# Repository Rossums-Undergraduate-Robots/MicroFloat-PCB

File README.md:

# MicroFloat-PCB
PCB CAD for MicroFloat

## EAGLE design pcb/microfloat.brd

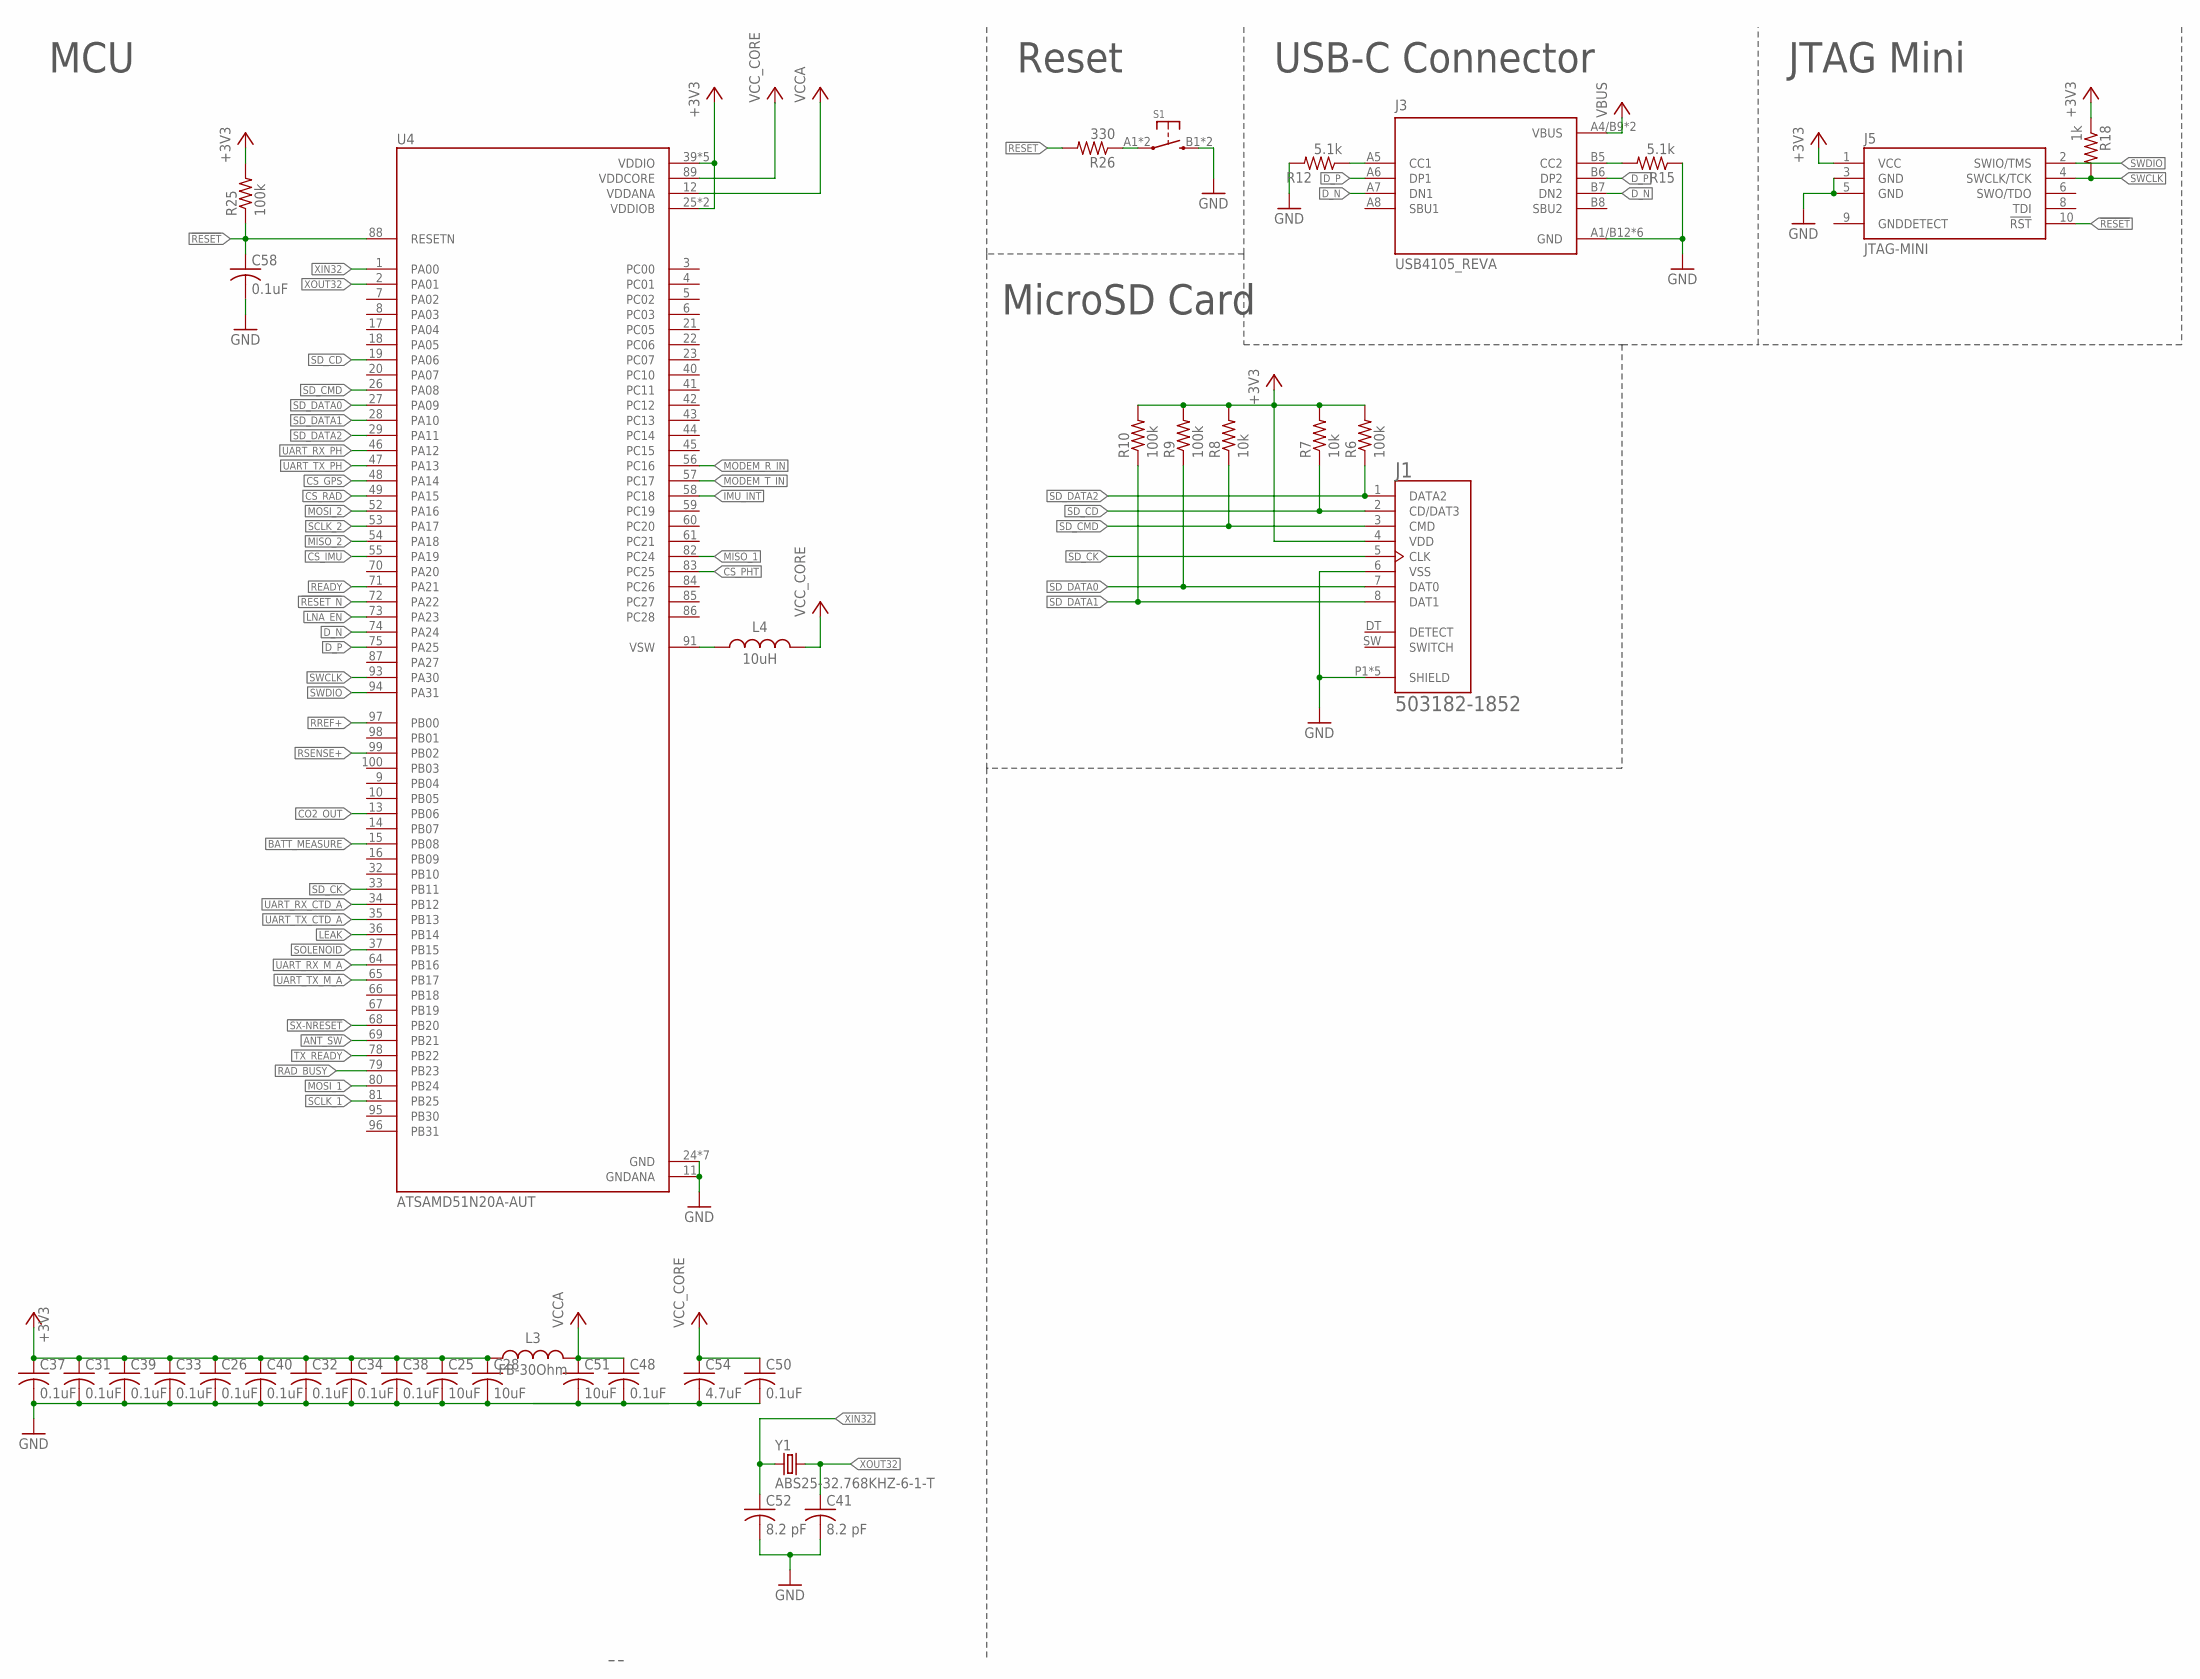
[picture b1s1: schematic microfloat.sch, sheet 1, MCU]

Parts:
C25, C28, C51: 10uF; C0805; TOLERANCE 5%; VOLTAGE 10V
C26, C31, C32, C33, C34, C37, C38, C39, C40, C48, C50, C58: 0.1uF; C0603; TOLERANCE 5%; VOLTAGE 10V
C41, C52: 8.2 pF; C0603; TOLERANCE 0.5%; VOLTAGE 10V
C54: 4.7uF; C0603; TOLERANCE 5%; VOLTAGE 10V
J1: 503182-1852; MOLEX_503182-1852
J3: USB4105_REVA; GCT_USB4105_REVA
J5: JTAG-MINI; FTSH-105-01-F-D-K
L3: FB-30Ohm; 0805; TOLERANCE 25%
L4: 10uH; 78438336100; TOLERANCE 10%
R6, R9, R10, R25: 100k; R0603; TOLERANCE 1%
R7, R8: 10k; R0603; TOLERANCE 1%
R12, R15: 5.1k; R0603; TOLERANCE 0.1%
R18: 1k; R0603; TOLERANCE 1%
R26: 330; R0603; TOLERANCE 1%
S1: BTN_10-XXSMD; TACTILE_SWITCH_SMD_6.2MM_TALL
U4: ATSAMD51N20A-AUT; QFP50P1600X1600X120-100N
Y1: ABS25-32.768KHZ-6-1-T; XTAL_ABS25-32.768KHZ-6-1-T

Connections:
!RESET: C58.1, J5.10 (!RST), R25.1, R26.2, U4.88 (RESETN)
!RESET_N: U4.72 (PA22); also elsewhere on the board
!SX-NRESET: U4.68 (PB20); also elsewhere on the board
+3V3: C25.1, C26.1, C28.1, C31.1, C32.1, C33.1, C34.1, C37.1, C38.1, C39.1, C40.1, J1.4 (VDD), J5.1 (VCC), L3.1, R6.2, R7.2, R8.2, R9.2, R10.2, R18.1, R25.2, U4.25 (VDDIOB), U4.30 (VDDIOB), U4.39 (VDDIO), U4.51 (VDDIO), U4.63 (VDDIO), U4.77 (VDDIO), U4.92 (VDDIO); also elsewhere on the board
ANT_SW: U4.69 (PB21); also elsewhere on the board
BATT_MEASURE: U4.15 (PB08); also elsewhere on the board
CO2_OUT: U4.13 (PB06); also elsewhere on the board
CS_GPS: U4.48 (PA14); also elsewhere on the board
CS_IMU: U4.55 (PA19); also elsewhere on the board
CS_PHT: U4.83 (PC25); also elsewhere on the board
CS_RAD: U4.49 (PA15); also elsewhere on the board
D_N: J3.A7 (DN1), J3.B7 (DN2), U4.74 (PA24)
D_P: J3.A6 (DP1), J3.B6 (DP2), U4.75 (PA25)
GND: C25.2, C26.2, C28.2, C31.2, C32.2, C33.2, C34.2, C37.2, C38.2, C39.2, C40.2, C41.2, C48.2, C50.2, C51.2, C52.2, C54.2, C58.2, J1.6 (VSS), J1.P1 (SHIELD), J1.P2 (SHIELD), J1.P3 (SHIELD), J1.P4 (SHIELD), J1.P5 (SHIELD), J3.A1/B12 (GND), J3.B1/A12 (GND), J3.G1 (GND), J3.G2 (GND), J3.G3 (GND), J3.G4 (GND), J5.3 (GND), J5.5 (GND), R12.2, R15.1, S1.B1 (S), S1.B2 (S), U4.11 (GNDANA), U4.24 (GND), U4.31 (GND), U4.38 (GND), U4.50 (GND), U4.62 (GND), U4.76 (GND), U4.90 (GND); also elsewhere on the board
IMU_INT: U4.58 (PC18); also elsewhere on the board
LEAK: U4.36 (PB14); also elsewhere on the board
LNA_EN: U4.73 (PA23); also elsewhere on the board
MISO_1: U4.82 (PC24); also elsewhere on the board
MISO_2: U4.54 (PA18); also elsewhere on the board
MODEM_R_IN: U4.56 (PC16); also elsewhere on the board
MODEM_T_IN: U4.57 (PC17); also elsewhere on the board
MOSI_1: U4.80 (PB24); also elsewhere on the board
MOSI_2: U4.52 (PA16); also elsewhere on the board
unnamed: J3.B5 (CC2), R15.2
unnamed: J3.A5 (CC1), R12.1
unnamed: L4.2, U4.91 (VSW)
unnamed: R26.1, S1.A1, S1.A2
RAD_BUSY: U4.79 (PB23); also elsewhere on the board
READY: U4.71 (PA21); also elsewhere on the board
RREF+: U4.97 (PB00); also elsewhere on the board
RSENSE+: U4.99 (PB02); also elsewhere on the board
SCLK_1: U4.81 (PB25); also elsewhere on the board
SCLK_2: U4.53 (PA17); also elsewhere on the board
SD_CD: J1.2 (CD/DAT3), R7.1, U4.19 (PA06)
SD_CK: J1.5 (CLK), U4.33 (PB11)
SD_CMD: J1.3 (CMD), R8.1, U4.26 (PA08)
SD_DATA0: J1.7 (DAT0), R9.1, U4.27 (PA09)
SD_DATA1: J1.8 (DAT1), R10.1, U4.28 (PA10)
SD_DATA2: J1.1 (DATA2), R6.1, U4.29 (PA11)
SOLENOID: U4.37 (PB15); also elsewhere on the board
SWCLK: J5.4 (SWCLK/TCK), R18.2, U4.93 (PA30)
SWDIO: J5.2 (SWIO/TMS), U4.94 (PA31)
TX_READY: U4.78 (PB22); also elsewhere on the board
UART_RX_CTD_A: U4.34 (PB12); also elsewhere on the board
UART_RX_M_A: U4.64 (PB16); also elsewhere on the board
UART_RX_PH: U4.46 (PA12); also elsewhere on the board
UART_TX_CTD_A: U4.35 (PB13); also elsewhere on the board
UART_TX_M_A: U4.65 (PB17); also elsewhere on the board
UART_TX_PH: U4.47 (PA13); also elsewhere on the board
VBUS: J3.A4/B9 (VBUS), J3.B4/A9 (VBUS); also elsewhere on the board
VCCA: C48.1, C51.1, L3.2, U4.12 (VDDANA)
VCC_CORE: C50.1, C54.1, L4.1, U4.89 (VDDCORE)
XIN32: C52.1, U4.1 (PA00), Y1.1
XOUT32: C41.1, U4.2 (PA01), Y1.4 (2)

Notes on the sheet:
MCU
Reset
MicroSD Card
USB-C Connector
JTAG Mini

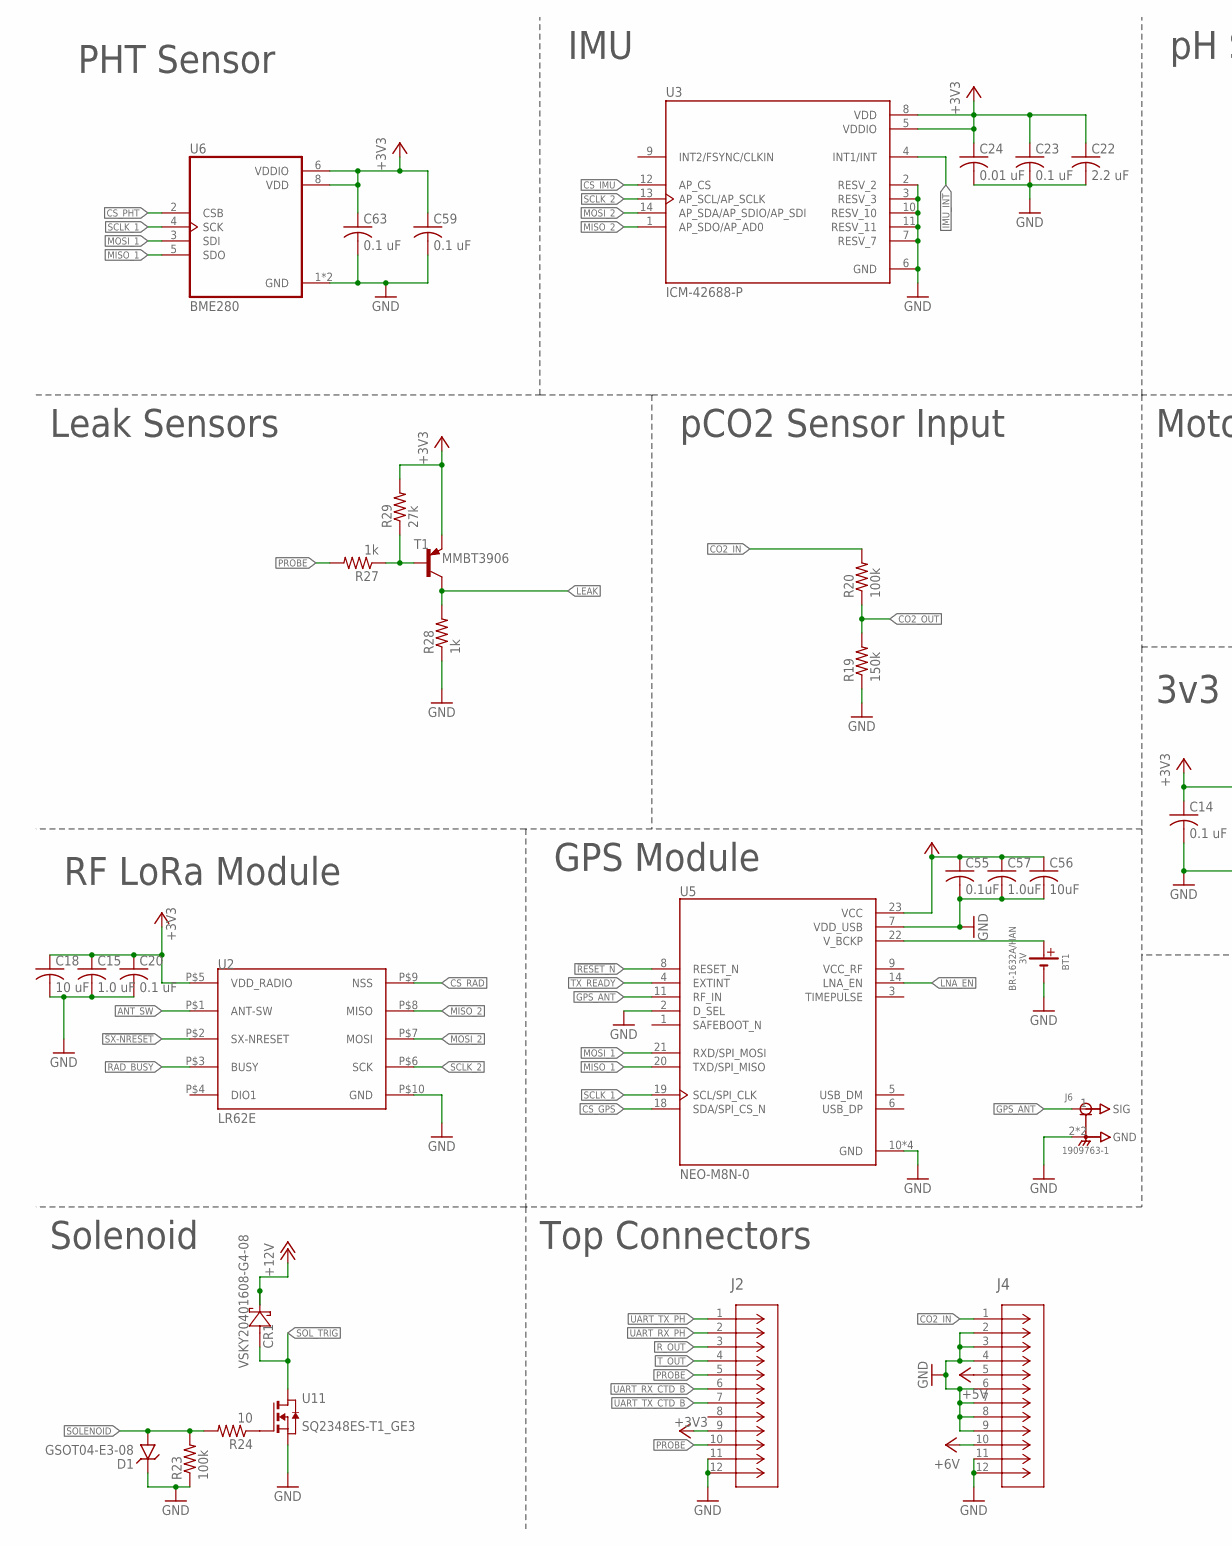
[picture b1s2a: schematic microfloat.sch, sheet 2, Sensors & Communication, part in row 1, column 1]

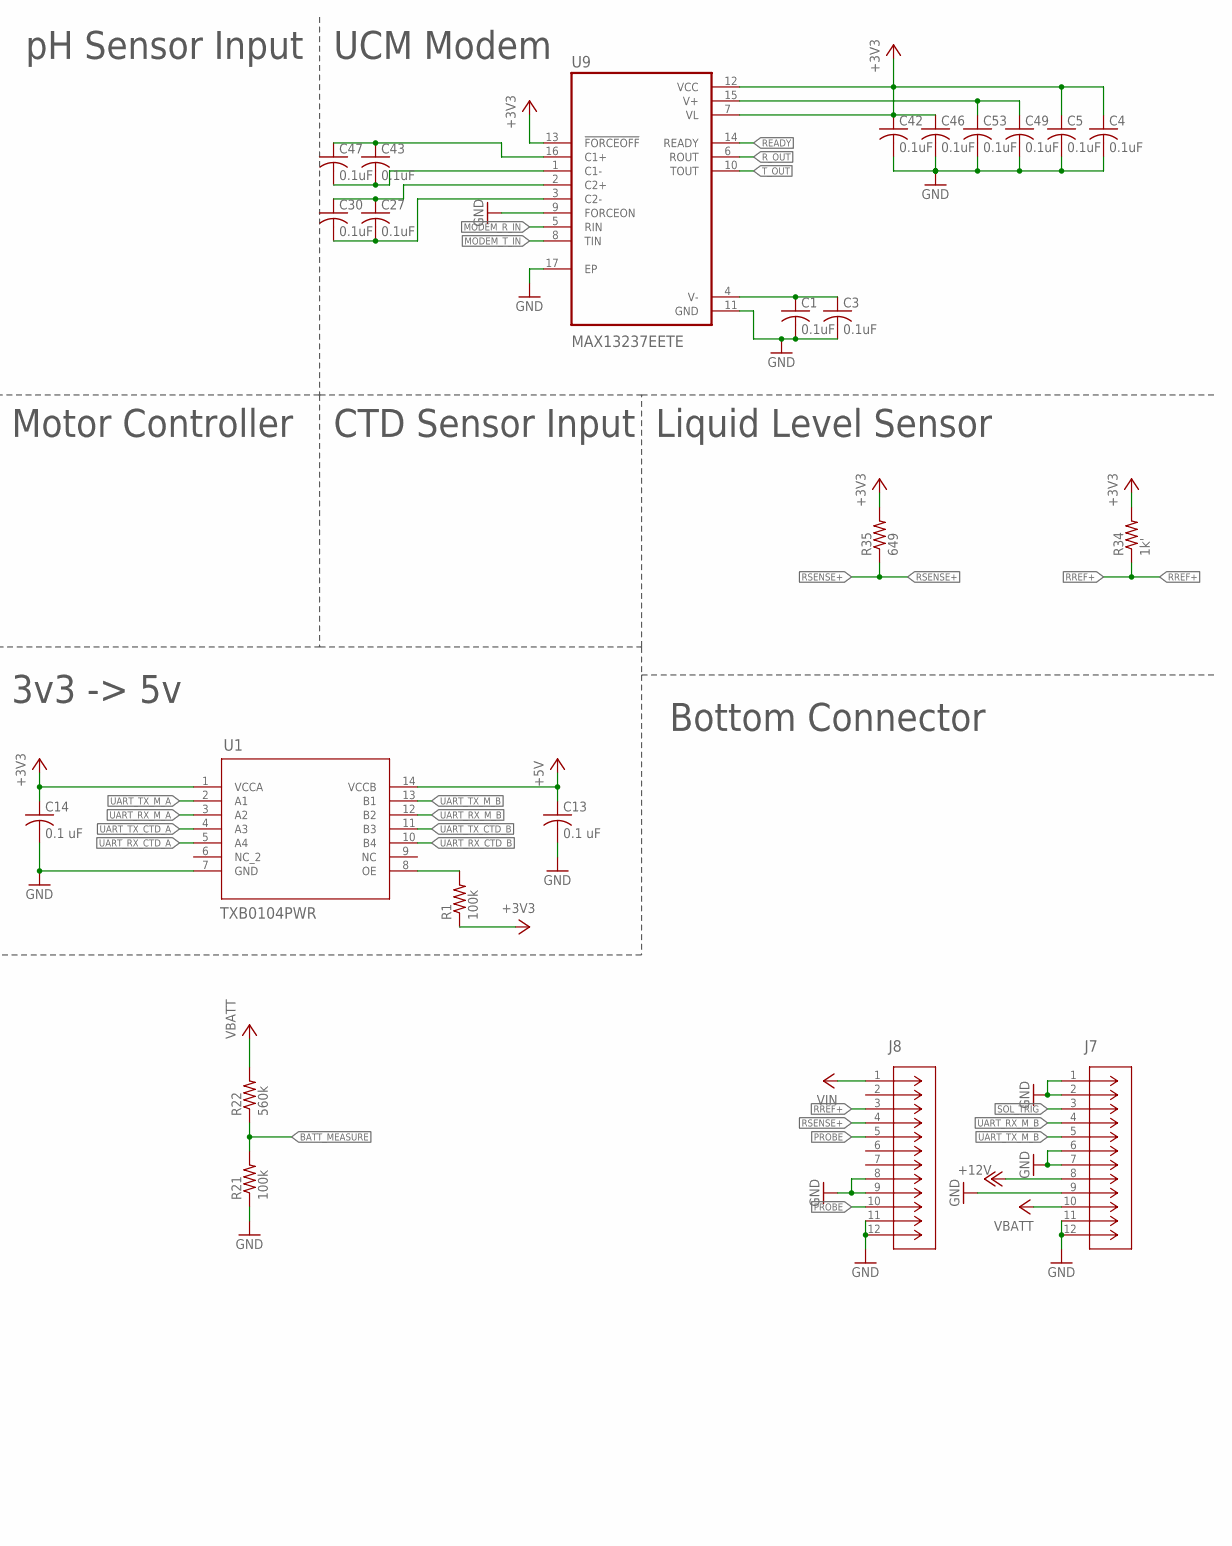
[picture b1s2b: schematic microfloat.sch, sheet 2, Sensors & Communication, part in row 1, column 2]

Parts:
BT1: BATTERY; BR-1632A/HAN
C1, C3, C4, C5, C27, C30, C42, C43, C46, C47, C49, C53, C55: 0.1uF; C0603; TOLERANCE 5%; VOLTAGE 10V
C13, C14, C20, C23, C59, C63: 0.1 uF; C0603; TOLERANCE 5%; VOLTAGE 10V
C15: 1.0 uF; C0603; TOLERANCE 5%; VOLTAGE 10V
C18: 10 uF; C0603; TOLERANCE 5%; VOLTAGE 10V
C22: 2.2 uF; C0603; TOLERANCE 5%; VOLTAGE 10V
C24: 0.01 uF; C0603; TOLERANCE 5%; VOLTAGE 10V
C56: 10uF; C0603; TOLERANCE 5%; VOLTAGE 10V
C57: 1.0uF; C0603; TOLERANCE 5%; VOLTAGE 10V
CR1: VSKY20401608-G4-08; CLP1608-2L_VIS
D1: GSOT04-E3-08; SOT-23-3
J2, J4, J7, J8: 1054291110; CON_1054291110_MOL
J6: 1909763-1; TE_1909763-1
R1, R23: 100k; R0603; TOLERANCE 1%
R19: 150k; R0603; TOLERANCE 0.1%
R20, R21: 100k; R0603; TOLERANCE 0.1%
R22: 560k; R0603; TOLERANCE 0.1%
R24: 10; R0603; TOLERANCE 1%
R27, R28: 1k; R0603; TOLERANCE 1%
R29: 27k; R0603; TOLERANCE 1%
R34: 1k'; R0603; TOLERANCE 0.1%
R35: 649; R0603; TOLERANCE 0.1%
T1: MMBT3906; SOT23-BEC
U1: TXB0104PWR; PW14
U2: LR62E
U3: ICM-42688-P; PQFN50P300X250X97-14N
U5: NEO-M8N-0; XCVR_NEO-M8N-0
U6: BME280; PSON65P250X250X100-8N
U9: MAX13237EETE; QFN80P500X500X80-17N
U11: SQ2348ES-T1_GE3; SOT-23-3

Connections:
!RESET_N: U5.8 (RESET_N); also elsewhere on the board
!SX-NRESET: U2.P$2 (SX-NRESET); also elsewhere on the board
+3V3: C4.1, C5.1, C14.1, C15.1, C18.1, C20.1, C22.1, C23.1, C24.1, C42.1, C46.1, C55.1, C56.1, C57.1, C59.1, C63.1, J2.9, R1.1, R29.2, R34.2, R35.2, T1.E, U1.1 (VCCA), U2.P$5 (VDD_RADIO), U3.5 (VDDIO), U3.8 (VDD), U5.23 (VCC), U6.6 (VDDIO), U6.8 (VDD), U9.7 (VL), U9.12 (VCC), U9.13 (!FORCEOFF); also elsewhere on the board
+5V: C13.1, J4.5, U1.14 (VCCB); also elsewhere on the board
+6V: J4.10; also elsewhere on the board
+12V: CR1.1 (11), J7.8; also elsewhere on the board
ANT_SW: U2.P$1 (ANT-SW); also elsewhere on the board
BATT_MEASURE: R21.2, R22.1; also elsewhere on the board
CO2_IN: J4.1, R20.2
CO2_OUT: R19.2, R20.1; also elsewhere on the board
CS_GPS: U5.18 (SDA/SPI_CS_N); also elsewhere on the board
CS_IMU: U3.12 (AP_CS); also elsewhere on the board
CS_PHT: U6.2 (CSB); also elsewhere on the board
CS_RAD: U2.P$9 (NSS); also elsewhere on the board
GND: BT1.- (MINUS), C1.2, C3.2, C4.2, C5.2, C13.2, C14.2, C15.2, C18.2, C20.2, C22.2, C23.2, C24.2, C42.2, C46.2, C49.2, C53.2, C55.2, C56.2, C57.2, C59.2, C63.2, D1.3 (C), J2.11, J2.12, J4.2, J4.3, J4.4, J4.6, J4.7, J4.8, J4.9, J4.11, J4.12, J6.2 (GND), J6.3 (GND), J7.1, J7.2, J7.6, J7.7, J7.9, J7.11, J7.12, J8.8, J8.9, J8.11, J8.12, R19.1, R21.1, R23.1, R28.1, U1.7 (GND), U2.P$10 (GND), U3.2 (RESV_2), U3.3 (RESV_3), U3.6 (GND), U3.7 (RESV_7), U3.10 (RESV_10), U3.11 (RESV_11), U5.2 (D_SEL), U5.7 (VDD_USB), U5.10 (GND), U5.12 (GND), U5.13 (GND), U5.24 (GND), U6.1 (GND), U6.7 (GND), U9.9 (FORCEON), U9.11 (GND), U9.17 (EP), U11.2 (S); also elsewhere on the board
GPS_ANT: J6.1 (SIG), U5.11 (RF_IN)
IMU_INT: U3.4 (INT1/INT); also elsewhere on the board
LEAK: R28.2, T1.C; also elsewhere on the board
LNA_EN: U5.14 (LNA_EN); also elsewhere on the board
MISO_1: U5.20 (TXD/SPI_MISO), U6.5 (SDO); also elsewhere on the board
MISO_2: U2.P$8 (MISO), U3.1 (AP_SDO/AP_AD0); also elsewhere on the board
MODEM_R_IN: U9.5 (RIN); also elsewhere on the board
MODEM_T_IN: U9.8 (TIN); also elsewhere on the board
MOSI_1: U5.21 (RXD/SPI_MOSI), U6.3 (SDI); also elsewhere on the board
MOSI_2: U2.P$7 (MOSI), U3.14 (AP_SDA/AP_SDIO/AP_SDI); also elsewhere on the board
unnamed: R1.2, U1.8 (OE)
unnamed: C43.1, C47.1, U9.16 (C1+)
unnamed: R27.1, R29.1, T1.B
unnamed: C43.2, C47.2, U9.1 (C1-)
unnamed: C27.1, C30.1, U9.2 (C2+)
unnamed: C27.2, C30.2, U9.3 (C2-)
unnamed: C1.1, C3.1, U9.4 (V-)
unnamed: C49.1, C53.1, U9.15 (V+)
unnamed: R24.1, U11.1 (G)
unnamed: BT1.+ (PLUS), U5.22 (V_BCKP)
PROBE: J2.5, J2.10, J8.5, J8.10, R27.2
RAD_BUSY: U2.P$3 (BUSY); also elsewhere on the board
READY: U9.14 (READY); also elsewhere on the board
RREF+: J8.3, R34.1; also elsewhere on the board
RSENSE+: J8.4, R35.1; also elsewhere on the board
R_OUT: J2.3, U9.6 (ROUT)
SCLK_1: U5.19 (SCL/SPI_CLK), U6.4 (SCK); also elsewhere on the board
SCLK_2: U2.P$6 (SCK), U3.13 (AP_SCL/AP_SCLK); also elsewhere on the board
SOLENOID: D1.1 (A), R23.2, R24.2; also elsewhere on the board
SOL_TRIG: CR1.2 (12), J7.3, U11.3 (D)
TX_READY: U5.4 (EXTINT); also elsewhere on the board
T_OUT: J2.4, U9.10 (TOUT)
UART_RX_CTD_A: U1.5 (A4); also elsewhere on the board
UART_RX_CTD_B: J2.6, U1.10 (B4)
UART_RX_M_A: U1.3 (A2); also elsewhere on the board
UART_RX_M_B: J7.4, U1.12 (B2)
UART_RX_PH: J2.2; also elsewhere on the board
UART_TX_CTD_A: U1.4 (A3); also elsewhere on the board
UART_TX_CTD_B: J2.7, U1.11 (B3)
UART_TX_M_A: U1.2 (A1); also elsewhere on the board
UART_TX_M_B: J7.5, U1.13 (B1)
UART_TX_PH: J2.1; also elsewhere on the board
VBATT: J7.10, R22.2; also elsewhere on the board
VIN: J8.1; also elsewhere on the board

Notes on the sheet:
PHT Sensor
IMU
Leak Sensors
pCO2 Sensor Input
pH Sensor Input
GPS Module
RF LoRa Module
CTD Sensor Input
Liquid Level Sensor
Motor Controller
UCM Modem
Solenoid
3v3 -> 5v
Top Connectors
Bottom Connector

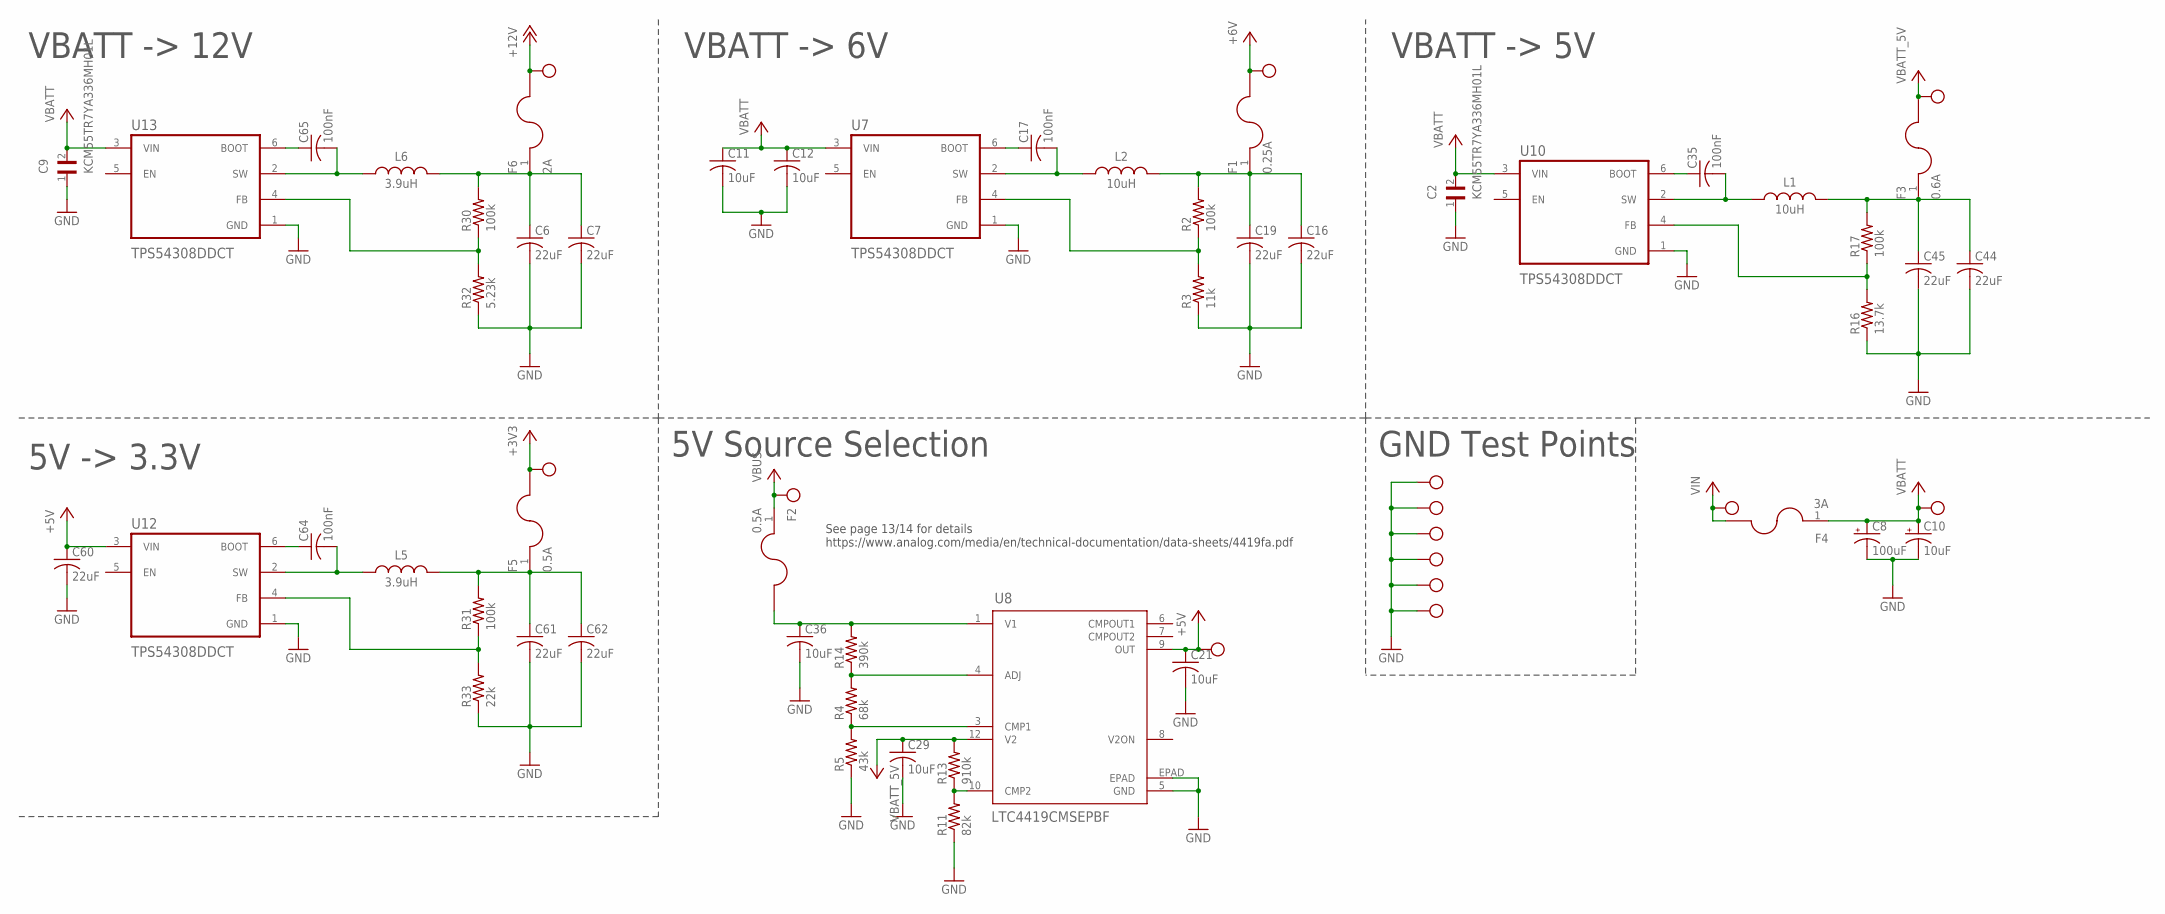
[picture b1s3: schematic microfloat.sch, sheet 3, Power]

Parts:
$$$$$$U$1, $$$$$$U$2, $$$$$$U$3, $$$$$$U$4, $$$$$$U$5, $$$$$$U$6: TEST_POINT
$$$$U$2, $$$$U$3, $$$$U$4, $$$$U$5: TEST_POINT
$$U$1, $$U$2, $$U$3, $$U$5: TEST_POINT
C2, C9: KCM55TR7YA336MH01L; CAPC6153X500N
C6, C7, C16, C19: 22uF; C0805; TOLERANCE 5%; VOLTAGE 16V
C8: 100uF; E3,5-8; TOLERANCE 20%; VOLTAGE 25V
C10: 10uF; E2,5-5; TOLERANCE 20%; VOLTAGE 25V
C11, C12: 10uF; C0805; TOLERANCE 5%; VOLTAGE 35V
C17, C35, C65: 100nF; C0603; TOLERANCE 5%; VOLTAGE 16V
C21, C29, C36: 10uF; C0603; TOLERANCE 5%; VOLTAGE 10V
C44, C45, C60, C61, C62: 22uF; C0603; TOLERANCE 5%; VOLTAGE 10V
C64: 100nF; C0603; TOLERANCE 5%; VOLTAGE 10V
F1: 0.25A; F1206
F2, F5: 0.5A; F1206
F3: 0.6A; F1206
F4: 3A; F1206
F6: 2A; F1206
L1, L2: 10uH; 78438336100; TOLERANCE 10%
L5, L6: 3.9uH; SRR3818A-3R9Y; TOLERANCE 10%
R2, R17, R30, R31: 100k; R0603; TOLERANCE 1%
R3: 11k; R0603; TOLERANCE 1%
R4: 68k; R0603; TOLERANCE 0.1%
R5: 43k; R0603; TOLERANCE 0.1%
R11: 82k; R0603; TOLERANCE 0.1%
R13: 910k; R0603; TOLERANCE 0.1%
R14: 390k; R0603; TOLERANCE 0.1%
R16: 13.7k; R0603; TOLERANCE 1%
R32: 5.23k; R0603; TOLERANCE 1%
R33: 22k; R0603; TOLERANCE 1%
U7, U10, U12, U13: TPS54308DDCT; SOT95P280X110-6N
U8: LTC4419CMSEPBF; MSE_12_ADI

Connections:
+3V3: $$$$U$5.P$1, F5.2; also elsewhere on the board
+5V: $$$$U$4.P$1, C21.1, C60.1, U8.9 (OUT), U12.3 (VIN); also elsewhere on the board
+6V: $$$$U$3.P$1, F1.2; also elsewhere on the board
+12V: $$U$5.P$1, F6.2; also elsewhere on the board
GND: $$$$$$U$4.P$1, $$$$$$U$5.P$1, $$$$U$2.P$1, $$U$1.P$1, $$U$2.P$1, $$U$3.P$1, C2.1, C6.2, C7.2, C8.-, C9.1, C10.-, C11.2, C12.2, C16.2, C19.2, C21.2, C29.2, C36.2, C44.2, C45.2, C60.2, C61.2, C62.2, R3.1, R5.1, R11.1, R16.1, R32.1, R33.1, U7.1 (GND), U8.5 (GND), U8.EPAD, U10.1 (GND), U12.1 (GND), U13.1 (GND); also elsewhere on the board
unnamed: C35.1, U10.6 (BOOT)
unnamed: C35.2, L1.2, U10.2 (SW)
unnamed: R16.2, R17.1, U10.4 (FB)
unnamed: C64.1, U12.6 (BOOT)
unnamed: C64.2, L5.1, U12.2 (SW)
unnamed: R31.1, R33.2, U12.4 (FB)
unnamed: C6.1, C7.1, F6.1, L6.2, R30.2
unnamed: C16.1, C19.1, F1.1, L2.1, R2.2
unnamed: C44.1, C45.1, F3.1, L1.1, R17.2
unnamed: C61.1, C62.1, F5.1, L5.2, R31.2
unnamed: R4.2, R14.1, U8.4 (ADJ)
unnamed: R4.1, R5.2, U8.3 (CMP1)
unnamed: R11.2, R13.1, U8.10 (CMP2)
unnamed: C36.1, F2.2, R14.2, U8.1 (V1)
unnamed: C65.1, U13.6 (BOOT)
unnamed: C65.2, L6.1, U13.2 (SW)
unnamed: R30.1, R32.2, U13.4 (FB)
unnamed: C17.1, U7.6 (BOOT)
unnamed: C17.2, L2.2, U7.2 (SW)
unnamed: R2.1, R3.2, U7.4 (FB)
VBATT: $$$$$$U$3.P$1, C2.2, C8.+, C9.2, C10.+, C11.1, C12.1, F4.1, U7.3 (VIN), U10.3 (VIN), U13.3 (VIN); also elsewhere on the board
VBATT_5V: $$$$$$U$2.P$1, C29.1, F3.2, R13.2, U8.12 (V2)
VBUS: $$$$$$U$1.P$1, F2.1; also elsewhere on the board
VIN: $$$$$$U$6.P$1, F4.2; also elsewhere on the board

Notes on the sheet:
VBATT -> 12V
VBATT -> 6V
VBATT -> 5V
5V -> 3.3V
5V Source Selection
GND Test Points
See page 13/14 for details https://www.analog.com/media/en/technical-documentation/data-sheets/4419fa.pdf

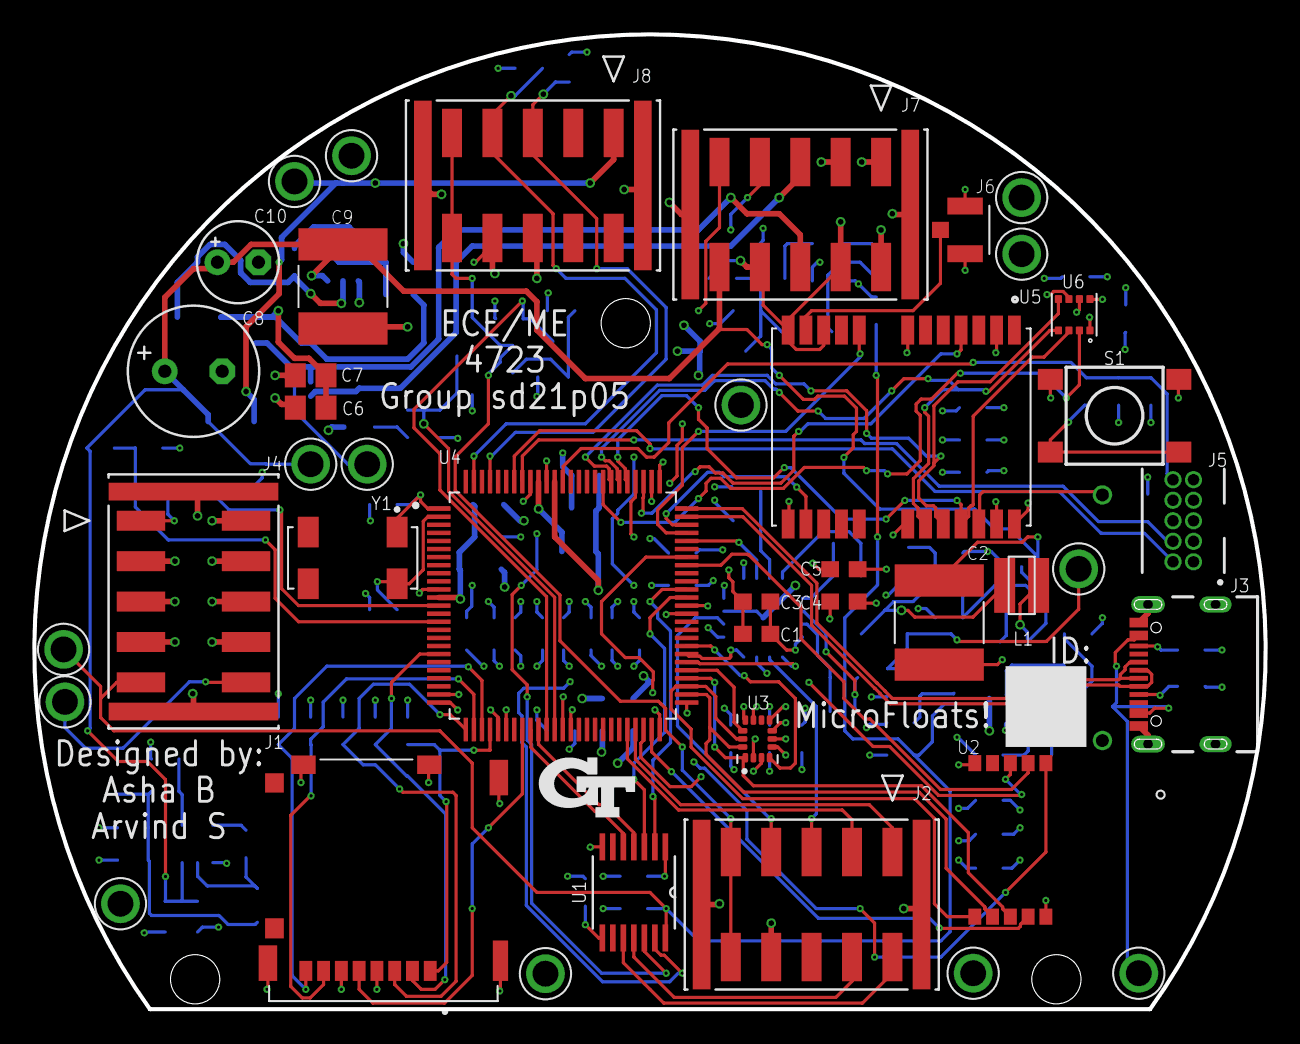
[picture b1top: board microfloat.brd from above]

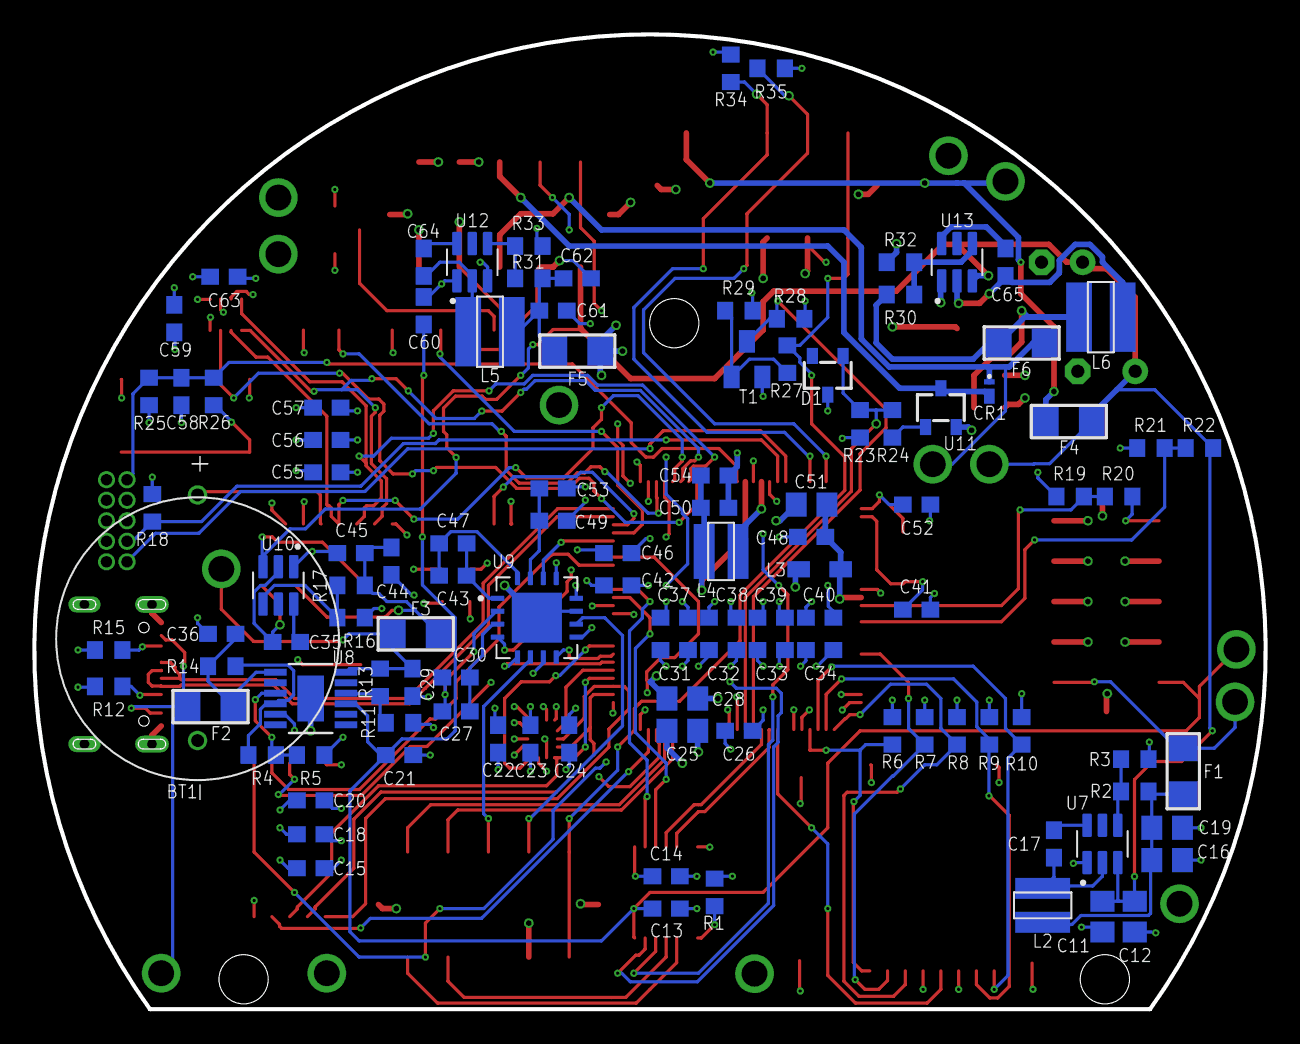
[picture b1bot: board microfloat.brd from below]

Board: 4 copper layers, 76.2 x 60.3 mm, 155 parts (112 on the bottom side), 100 nets.

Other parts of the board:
$$$$U$1: LOGO_GT_0.25"
U$1: UCM-MODEM

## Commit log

2021-02-27 blank pcb files
2021-03-01 added parts
2021-03-02 parts
2021-03-02 added atsamd51
2021-03-03 rf module
2021-03-03 usbc
2021-03-03 reset switch
2021-03-03 started schematic
2021-03-03 Connectors fun
2021-03-09 Regulator, plus TRS chip
2021-03-13 fun fun schematic progress
2021-03-13 fun fun fun
2021-03-14 More parts fun times
2021-03-15 schematic progress monday
2021-03-16 Updated library
2021-03-16 Final regulators
2021-03-17 manually merged parts yipee
2021-03-20 progress
2021-03-21 init sch
2021-03-22 wow i hatepcb design, routing is happening
2021-03-22 good enough
2021-03-23 locked dimension for CAD
2021-03-30 changes changes changes
2021-03-31 changessssssssss, mcu pinout
2021-04-03 Power wee
2021-04-03 more schematic changes (conn fix, solenoid fix, etc)
2021-04-04 Improved signal buffering on connectors and hi Asha
2021-04-04 ADC resolved
2021-04-04 More changes
2021-04-04 part of component placement done
2021-04-05 component placement near complete, need to fix connector, place test points
2021-04-05 removed values and moved stuff to top
2021-04-07 Work in progress
2021-04-07 Put final crystal part
2021-04-07 Final schematic with missing passives
2021-04-07 More placement
2021-04-07 Swapped capcitors into parallel
2021-04-07 Pain
2021-04-08 More pain
2021-04-08 Nvm more pain
2021-04-08 So much pain
2021-04-08 And so it goes
2021-04-08 Routing is hell
2021-04-08 The road to hell is paved with good intentions
2021-04-08 Coming together
2021-04-08 home stretch
2021-04-08 DRC being weird
2021-04-08 16 airwires and some weird ERC warnigns
2021-04-08 Make that 14
2021-04-08 fixed erc error
2021-04-08 Names are a thing
2021-04-09 no airwires, clearance issues, dimensions, wire stubs
2021-04-09 BEEG Capacitor
2021-04-09 Changes I think
2021-04-09 I hate inductors
2021-04-09 Last inductor to fix
2021-04-09 One last DRC error
2021-04-09 WEEEEEEEEEEEEEEEE
2021-04-09 What time is it
2021-04-09 Eagle crashed oh no
2021-04-09 Silkscreen bad
2021-04-09 Test poitns are cool
2021-04-09 And another one bites the dust
2021-04-09 Getting there
2021-04-09 Fixes for minor issues
2021-04-09 random wire stubs eagle bad who knows
2021-04-09 New inductors again
2021-04-09 I hate eagle
2021-04-09 GERBERS
2021-04-10 3d cad

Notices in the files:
parts and their libraries:
COPYRIGHT: Copyright (C) 2016 Accelerated Designs. All rights reserved
COPYRIGHT: Copyright (C) 2018 Accelerated Designs. All rights reserved
